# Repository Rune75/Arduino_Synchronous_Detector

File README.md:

# Arduino Synchronous Detector

This code demostrates a low frequency lockin amplifier or synchronous ligth detector inplementation using only a Arduino board and 2 additional modules: 
  1. The OPT101 amplified vissible light photodiode 
  2. A laser pointer 
  
The syncronous detector components are all realised in software 
using the Atmega328p builtin ADC as frontend and one GPIO for driving the laserdiode.

## Whys and hows
The idea behind a synchronous detector or lockin amplifier is best described trough an example. So lets asume we want to detect a moving target at some  distance. To be able to do this one could for example shine some ligth on the target and look for changes in the reflected light. If setting up this experiment with a light source and a photosensor we will soon discover that the reflected light variation we are trying to measure is not distingusable from variations in the ambient light level as shown in the top figure below. If we instead modulate our signal source with some frequency and lock our detector to the same frequency and phase we have what is called a synchronous detector. 

As shown below the synchronous demodulation process cancels out ambient noise and we are left with the signal of interest only.

Thie noise cancelation part is a bit hard to grasp in the frequncy domain, but if we instead consider that the modulated source is realy just swithing on an off the light source at a constant frequency, and thus on the receiver side the same bacground noise will be present in both halfperiodes of the signal, both when the ligth source is on and when it is off. The demodulator is just a multiplicator that multiplies the signal with a square waveform with amplitude +1 to -1. at the same frequencuy and phase as the source modulation. The +- multiplication basicaly flips the sign on the noise in each halfperiode so the noise average over time from the demodulator is close to zero. This process is shown in the following figure.

### Basic principle

### Analog implementation
The analog implenetation of a locking amplifier is shown below. These devices are built up around a oscilator and a RF mixer where the oscilator is source for both the exitation and the demodulator, this way it is always in phase lock.

### Full microcontroller inplementation with Atmega328p
Understanding that a RF mixer is realy just a multiplicator we see that we can easily implement this whole circut in a microcontroller as shown below. 

### Expanded view of actual implementation
By filtering the reflected signal while under exitation and the reflected signal when exitation is off in two separate arrays we are able to also measure and log the backround ligth level.

###  Sampling and signal bandwith (work in progress)
ADC raw samplerate with prescaler set to 16 in free running mode is 16 MHz/(16*13) ≈ 77kHz. estimated > 8 bit resoluition. 
(LSB is a bit unstable because of the high samplerate).
The resulution is then increased by 6 bit trough downsampling by 4^6 = 4096 giving us a downsampled samplerate of 77k / 4096 = 18.79Hz
The exitation pulse length is set to 16 samples and 50% dudty cycle so the Exitation pulse rate is 77kHz/(2*16) = ~2404Hz.
The bandwith of the opt101 sensor is 14KHz so 2.4kHz exitation frequency is wel within this band.

Ewerything is divided down from and synchronous to the ADC raw samplerate.

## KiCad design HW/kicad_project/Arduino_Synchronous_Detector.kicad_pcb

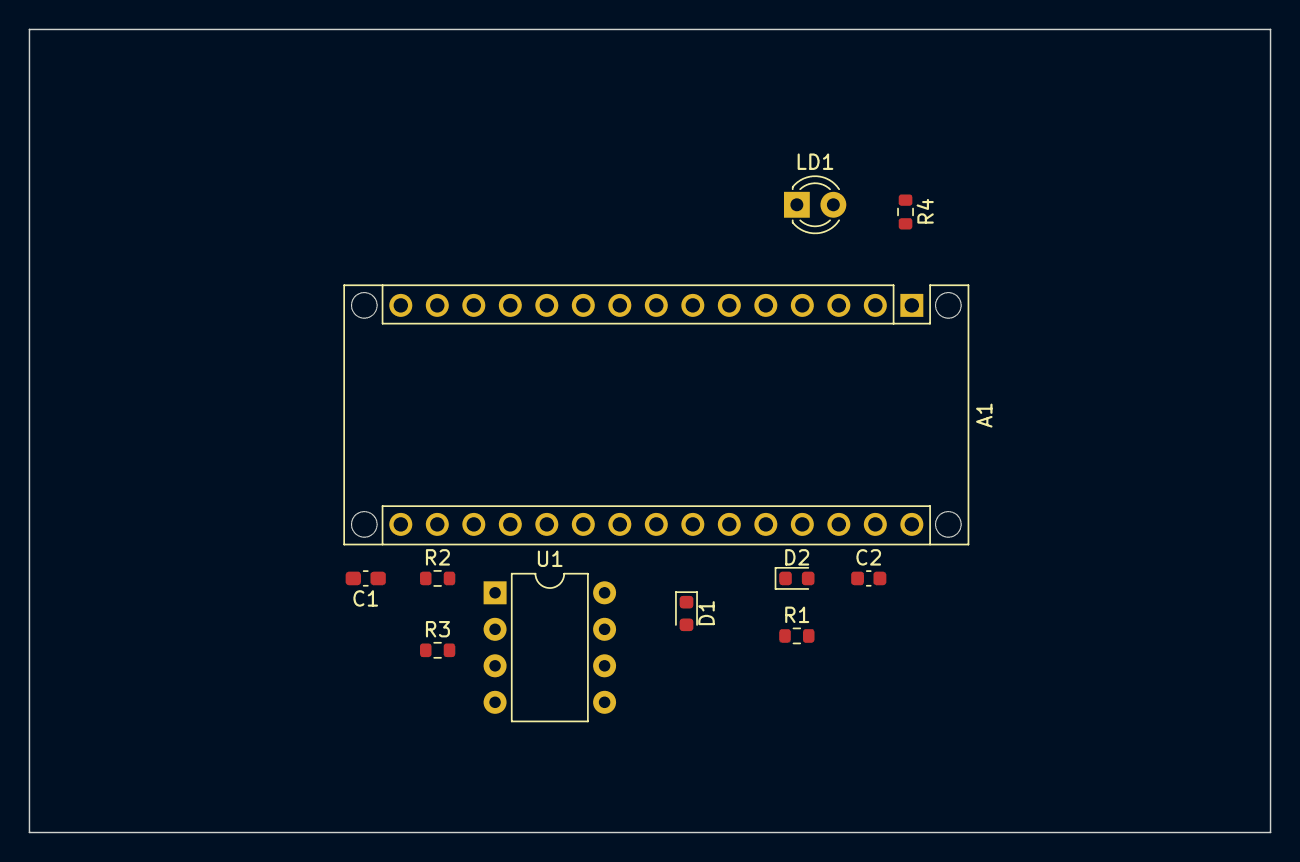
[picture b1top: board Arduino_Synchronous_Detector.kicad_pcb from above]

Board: 2 copper layers, 86.4 x 55.9 mm, 11 parts (0 on the bottom side), 9 nets, no tracks yet.

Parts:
A1: Arduino_Nano_v3.x; Arduino_Nano_WithMountingHoles
C1: C; C_0603_1608Metric_Pad1.08x0.95mm_HandSolder
C2: C; C_0603_1608Metric
D1, D2: D; D_0603_1608Metric
LD1: D_Laser_1A3C; LED_D3.0mm
R1: 10k; R_0603_1608Metric
R2, R3, R4: R; R_0603_1608Metric
U1: OPT101P; DIP-8_W7.62mm

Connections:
+12V: A1.30 (VIN), U1.1 (VS)
/5V: A1.27 (+5V), R1.1
GNDREF: A1.4 (GND), A1.29 (GND), C2.2, D2.1 (K), R3.2, R4.2, U1.3 (-V), U1.8 (COMMON)
unnamed: A1.19 (A0), C1.2, D1.1 (K)
unnamed: A1.20 (A1), R2.2, R3.1
unnamed: A1.5 (D2), LD1.1 (A)
unnamed: C2.1, D1.2 (A), D2.2 (A), R1.2
unnamed: LD1.2 (K), R4.1
unnamed: C1.1, R2.1, U1.4 (1MOHM_FB), U1.5 (OUTPUT)

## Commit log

2020-12-01 initial
2020-12-08 commit message
2020-12-10 uppdated signals
2020-12-10 uppdated drawing
2020-12-11 Update main.cpp
    Fixed some comments and found a bug in the sample code counter so made the code break compilation until I get that fixed.
2021-01-22 Delete FW directory
    restructured. placed unfinished code in develop branch
2021-04-22 set down the exitation frequency to ~~1.2kHz
2021-04-23 moved average calculation out of interupt
2021-04-24 added selection for calulating and showing background level
2021-04-24 added *.sal to .gitignore
2021-04-24 splited exitation responce and ambient levels in separate averagers
2021-04-24 fixed a comment
2021-04-26 renamed main.cpp
2021-04-26 setled on a multisouce folder structure
2021-10-25 added serial ploter
2021-11-05 cleaned up comments
2021-12-09 debug print
2022-03-27 lockin_detector.drawio
2022-03-27 Added lockin_detector-Signals.png
2022-03-27 Added lockin_detector-Signals_alt.drawio.png
2022-03-27 Added lockin_detector-Signals.drawio.png
2022-03-27 Updated spec
2022-03-27 updated .gitignore
2022-05-26 Added lockin_detector-Freq domain.drawio.png
2022-05-26 Added lockin_detector-Freq_domain.drawio.png
2022-05-26 updated specs
2023-11-20 added Kicad project
2023-11-22 Fixed typo
2023-11-22 Please continue from line 130
2023-11-24 Cleaned up comments and changed output print to teleplot
